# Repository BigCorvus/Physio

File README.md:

# Physio

My take on an (almost) open source development platform for a versatile wireless monitoring device that combines ECG, impedance pneumography, photoplethysmography, SPO2 calculation, galvanic skin response, NIBP wrist measurement as well as well as body temperature measurement in one wearable. 

Physio is based on a CK101 wrist blood pressure monitor, a CMS50C pulse oximeter, an ADS1292R analog front end for ECG and impedance pneumography (respiration monitoring via ECG electrodes), a MAX30205 human body temperature sensor and an ADXL345 accelerometer. The GSR measurement is also working fine so far, but it's interfering with the ADS1292R so only one of them can be used at a time. For instruction on hacking the CK101 and CMS50C see  my blog posts http://www.thinkering.de/cms/?p=833 and http://www.thinkering.de/cms/?p=864. and A Teensy 3.2 ties everythings together and uses an HC-05 bluetooth module for communication.
The carrier PCB of the current Physio version is designed for the great ADS1292R breakout board by protocentral->https://github.com/Protocentral/ADS1292rShield_Breakout

The Android app is based on the Amarino platform, so you have to download and install the Amarino App in order for this app to work (https://storage.googleapis.com/google-code-archive-downloads/v2/code.google.com/amarino/Amarino_2_v0_55.apk). The recording feature is not working yet and will be improved in the future.

In order to get the best ECG and respiration data I recommend placing the electrodes according to the "Einthoven II" lead.

Short demo video with crappy electrodes: https://youtu.be/U5jK3dh345U

Note: this is not a medical device, but a development platform for educational and research purposes. I'm assuming you know what you're doing.

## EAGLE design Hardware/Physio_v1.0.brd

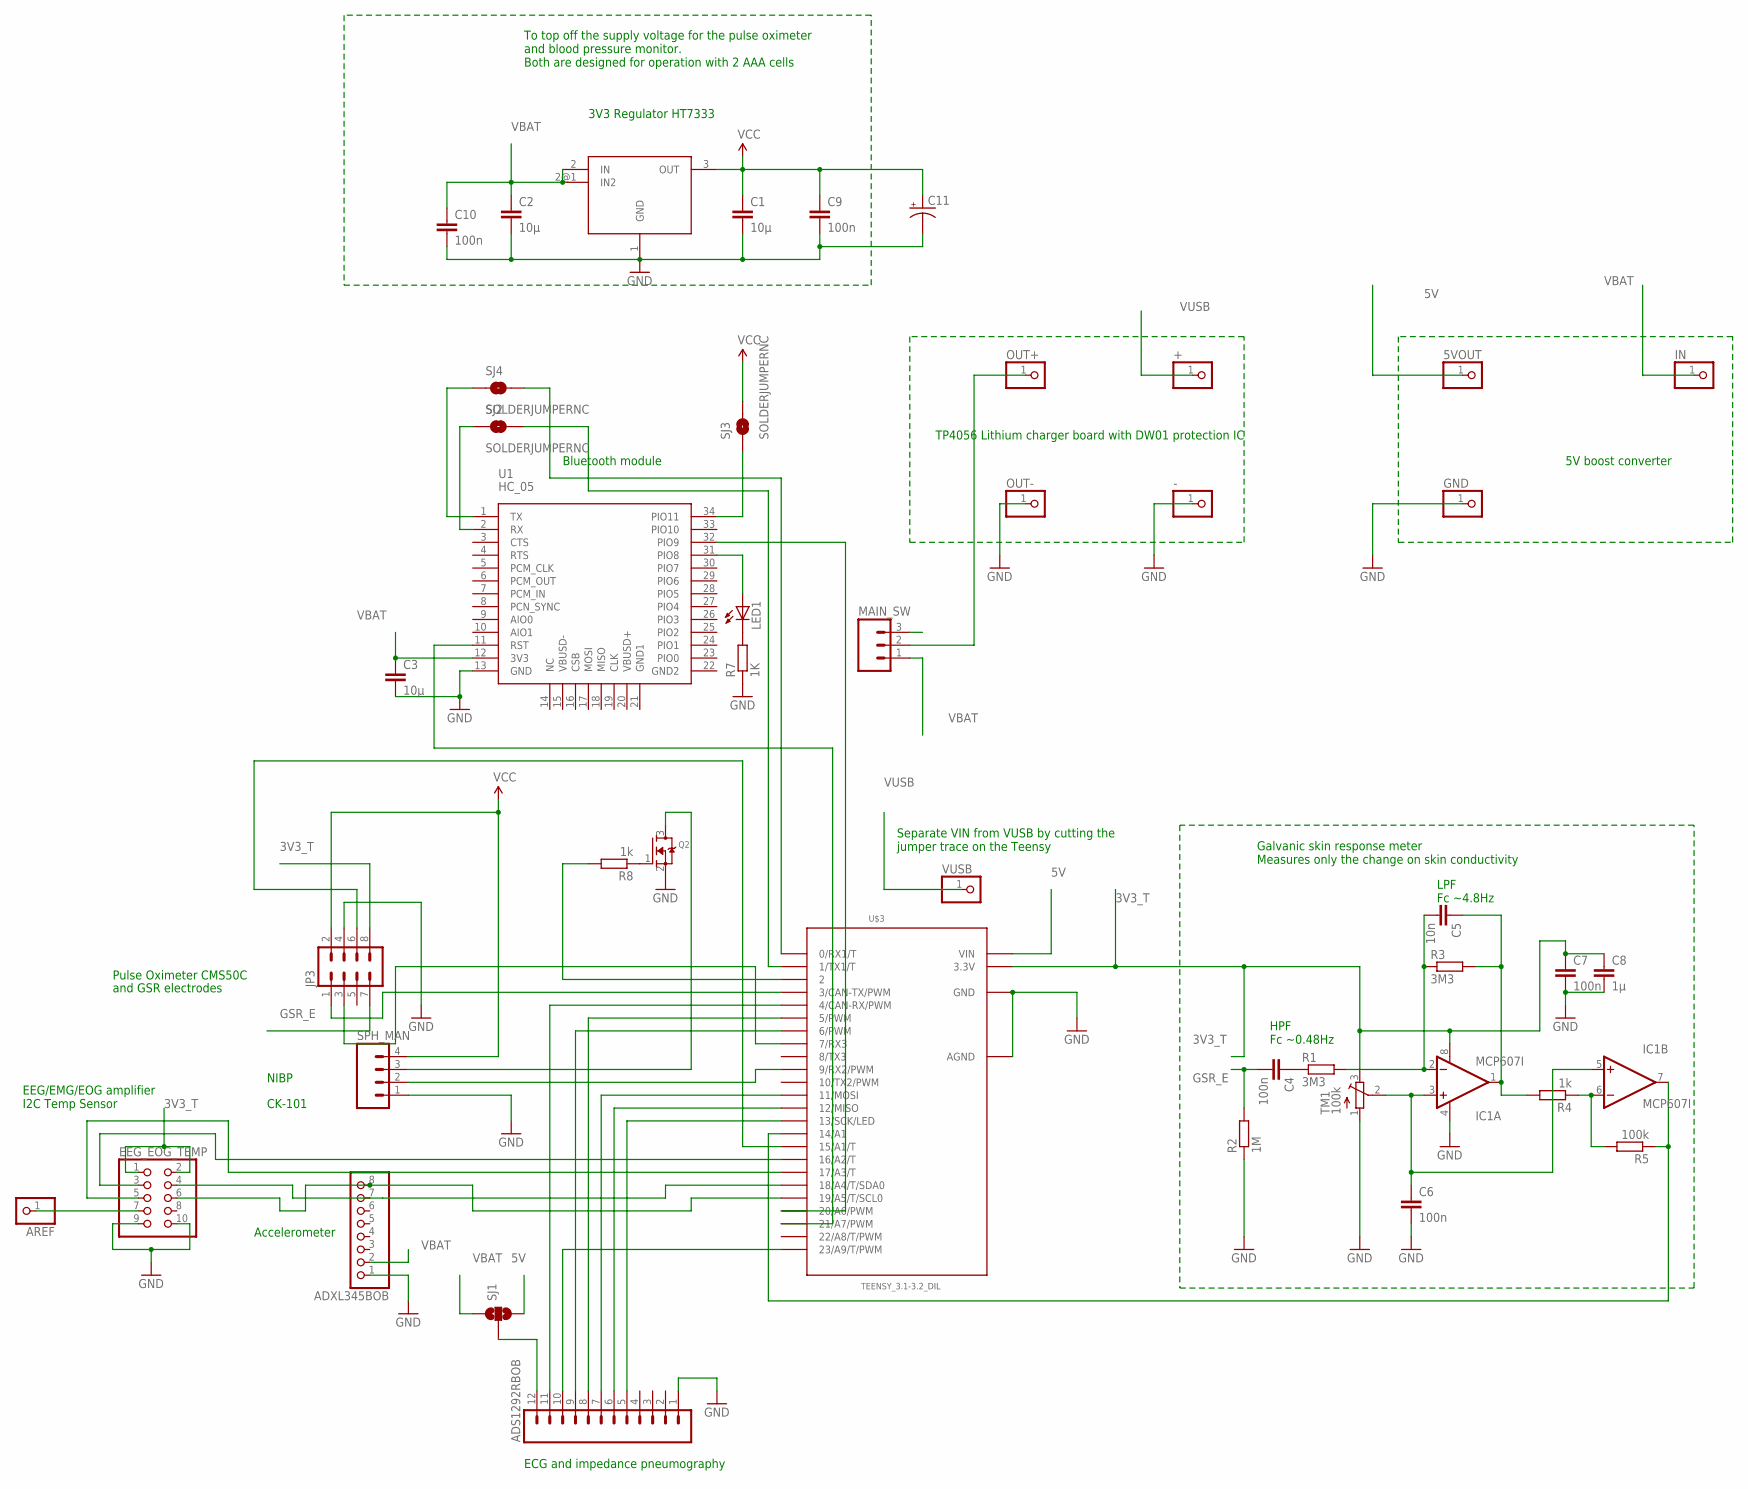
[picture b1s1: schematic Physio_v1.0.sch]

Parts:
5VOUT: PINHD-1X1; 1X01
+: PINHD-1X1; 1X01
-: PINHD-1X1; 1X01
ADS1292RBOB: M12PTH; 1X12
ADXL345BOB: PINHD-1X8CLEANBIG; 1X08-CLEANBIG
AREF: PINHD-1X1; 1X01
C1, C2, C3: 10µ; C0805K
C4, C6, C7, C9, C10: 100n; C0603K
C5: 10n; C0603K
C8: 1µ; C0603K
C11: CAP_POL7343; EIA7343
EEG_EOG_TEMP: PINHD-2X5/90; 2X05/90
GND: PINHD-1X1; 1X01
IC1: MCP607I; SO08
IN: PINHD-1X1; 1X01
JP3: M04X2; 2X4
LED1: LEDCHIP-LED0805; CHIP-LED0805
MAIN_SW: M03PTH; 1X03
OUT+: PINHD-1X1; 1X01
OUT-: PINHD-1X1; 1X01
Q2: MOSFET-NREFLOW; SOT23
R1, R3: 3M3; R0603
R2: 1M; R0603
R4, R8: 1k; R0603
R5: 100k; R0603
R7: 1K; R0603
SJ1: SOLDERJUMPER_2WAY-OLDT; SJ_2
SJ2, SJ3, SJ4: SOLDERJUMPERNC; SJ_2S
SPH_MAN: M04PTH; 1X04
TM1: 100k; TC33X
U1: HC_05; BLUETOOTH_SMD
U$2: HT7333; SOT89
U$3: TEENSY_3.1-3.2_DIL; TEENSY_3.0-3.2&LC_DIL
VUSB: PINHD-1X1; 1X01

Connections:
3V3_T: C7.1, C8.1, EEG_EOG_TEMP.1, EEG_EOG_TEMP.2, IC1.8 (V+), JP3.8, TM1.3 (E), U$3.3.3V
5V: 5VOUT.1, SJ1.3, U$3.VIN
GND: -.1, ADS1292RBOB.1, ADXL345BOB.1, C1.2, C2.2, C3.2, C6.2, C7.2, C8.2, C9.2, C10.2, C11.C (-), EEG_EOG_TEMP.9, EEG_EOG_TEMP.10, GND.1, IC1.4 (V-), JP3.4, OUT-.1, Q2.2 (S), R2.1, R7.1, SPH_MAN.1, TM1.1 (A), U1.13 (GND), U$2.1 (GND), U$3.AGND, U$3.GND
GSR_E: C4.2, JP3.7, R2.2
unnamed: JP3.1, U$3.3 (3/CAN-TX/PWM)
unnamed: SPH_MAN.2, U$3.9 (9/RX2/PWM)
unnamed: JP3.3, U$3.7 (7/RX3)
unnamed: Q2.3 (D), SPH_MAN.3
unnamed: SJ4.2, U$3.0 (0/RX1/T)
unnamed: SJ2.2, U$3.1 (1/TX1/T)
unnamed: ADS1292RBOB.7, U$3.11 (11/MOSI)
unnamed: ADS1292RBOB.6, U$3.12 (12/MISO)
unnamed: ADS1292RBOB.5, U$3.13 (13/SCK/LED)
unnamed: ADS1292RBOB.9, U$3.6 (6/PWM)
unnamed: ADS1292RBOB.8, U$3.5 (5/PWM)
unnamed: ADS1292RBOB.11, U$3.4 (4/CAN-RX/PWM)
unnamed: ADS1292RBOB.10, U$3.23/A9 (23/A9/T/PWM)
unnamed: C5.2, IC1.2 (-IN), R1.2, R3.1
unnamed: C5.1, IC1.1 (OUT), R3.2, R4.2
unnamed: C6.1, IC1.3 (+IN), IC1.5 (+IN), TM1.2 (S)
unnamed: C4.1, R1.1
unnamed: SJ4.1, U1.1 (TX)
unnamed: IC1.6 (-IN), R4.1, R5.2
unnamed: IC1.7 (OUT), R5.1, U$3.14/A0 (14/A1)
unnamed: SJ2.1, U1.2 (RX)
unnamed: JP3.6, U$3.15/A1 (15/A1/T)
unnamed: ADXL345BOB.8, EEG_EOG_TEMP.6, U$3.19/A5 (19/A5/T/SCL0)
unnamed: ADXL345BOB.7, EEG_EOG_TEMP.4, U$3.18/A4 (18/A4/T/SDA0)
unnamed: LED1.C, R7.2
unnamed: LED1.A, U1.31 (PIO8)
unnamed: EEG_EOG_TEMP.3, U$3.16/A2 (16/A2/T)
unnamed: EEG_EOG_TEMP.5, U$3.17/A3 (17/A3/T)
unnamed: R8.2, U$3.2
unnamed: ADS1292RBOB.12, SJ1.2
unnamed: Q2.1 (G), R8.1
unnamed: AREF.1, EEG_EOG_TEMP.7
unnamed: MAIN_SW.2, OUT+.1
unnamed: U1.32 (PIO9), U$3.20/A6 (20/A6/PWM)
unnamed: U1.11 (RST), U$3.21/A7 (21/A7/PWM)
unnamed: SJ3.1, U1.34 (PIO11)
VBAT: ADXL345BOB.2, C2.1, C3.1, C10.1, IN.1, MAIN_SW.1, SJ1.1, U1.12 (3V3), U$2.2 (IN), U$2.2@1 (IN2)
VCC: C1.1, C9.1, C11.A (+), JP3.2, SJ3.2, SPH_MAN.4, U$2.3 (OUT)
VUSB: +.1, VUSB.1

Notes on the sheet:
Galvanic skin response meter Measures only the change on skin conductivity
HPF Fc ~0.48Hz
LPF Fc ~4.8Hz
ECG and impedance pneumography
Accelerometer
NIBP
CK-101
Pulse Oximeter CMS50C
EEG/EMG/EOG amplifier I2C Temp Sensor
3V3 Regulator HT7333
Separate VIN from VUSB by cutting the jumper trace on the Teensy
TP4056 Lithium charger board with DW01 protection IC
5V boost converter
To top off the supply voltage for the pulse oximeter and blood pressure monitor. Both are designed for operation with 2 AAA cells
Bluetooth module
and GSR electrodes

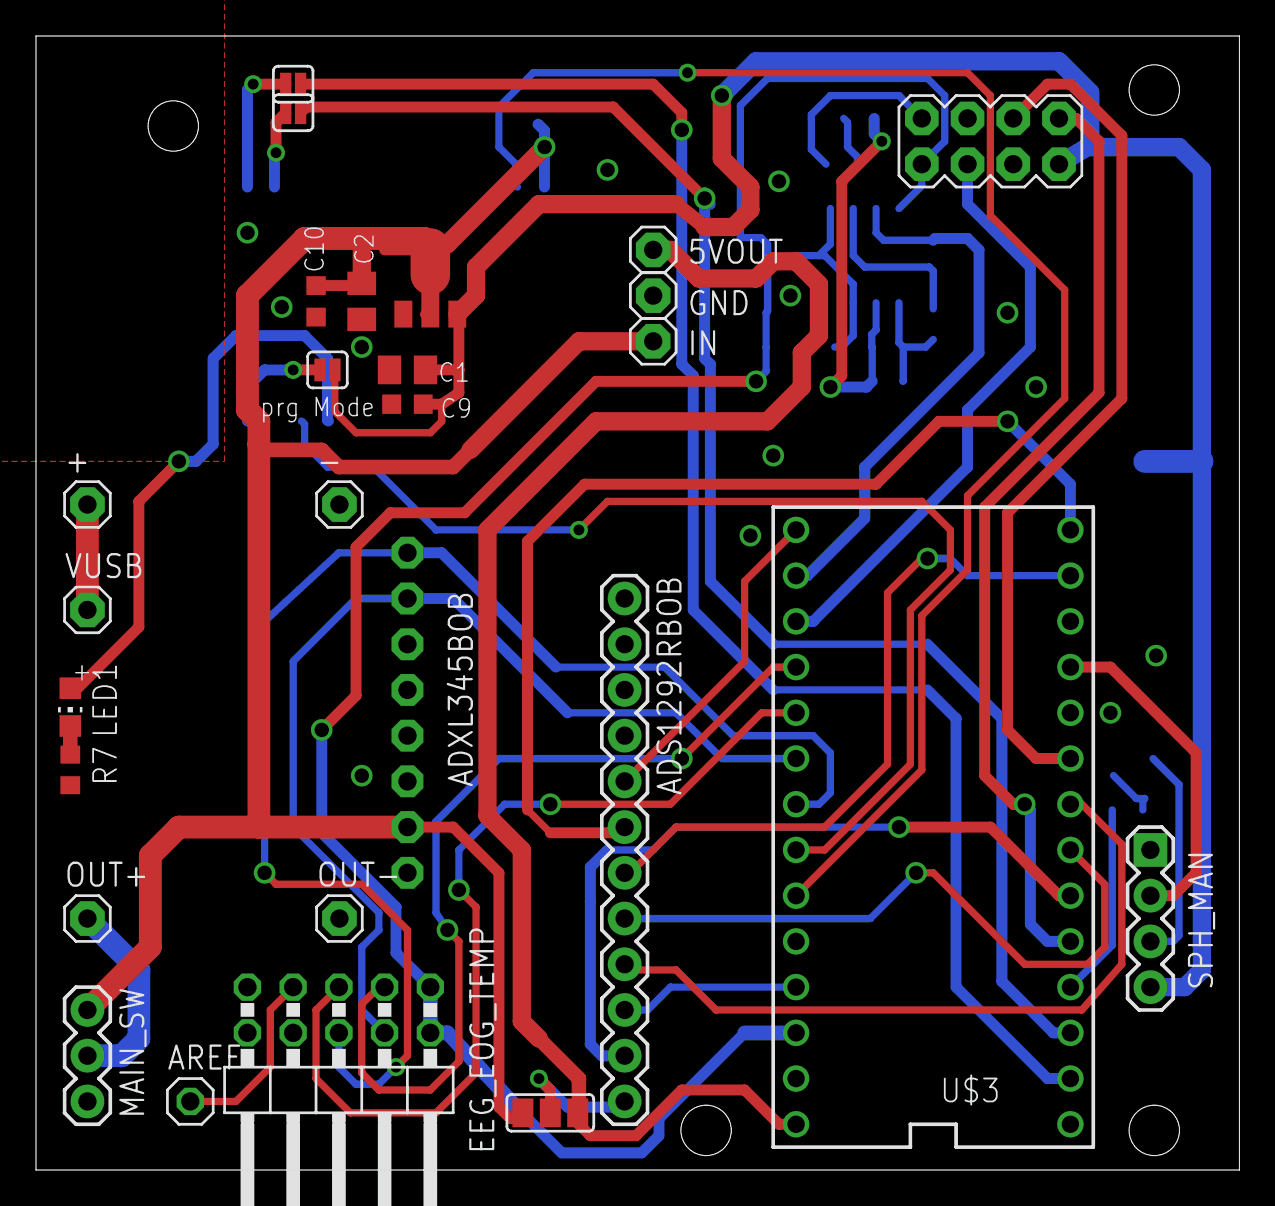
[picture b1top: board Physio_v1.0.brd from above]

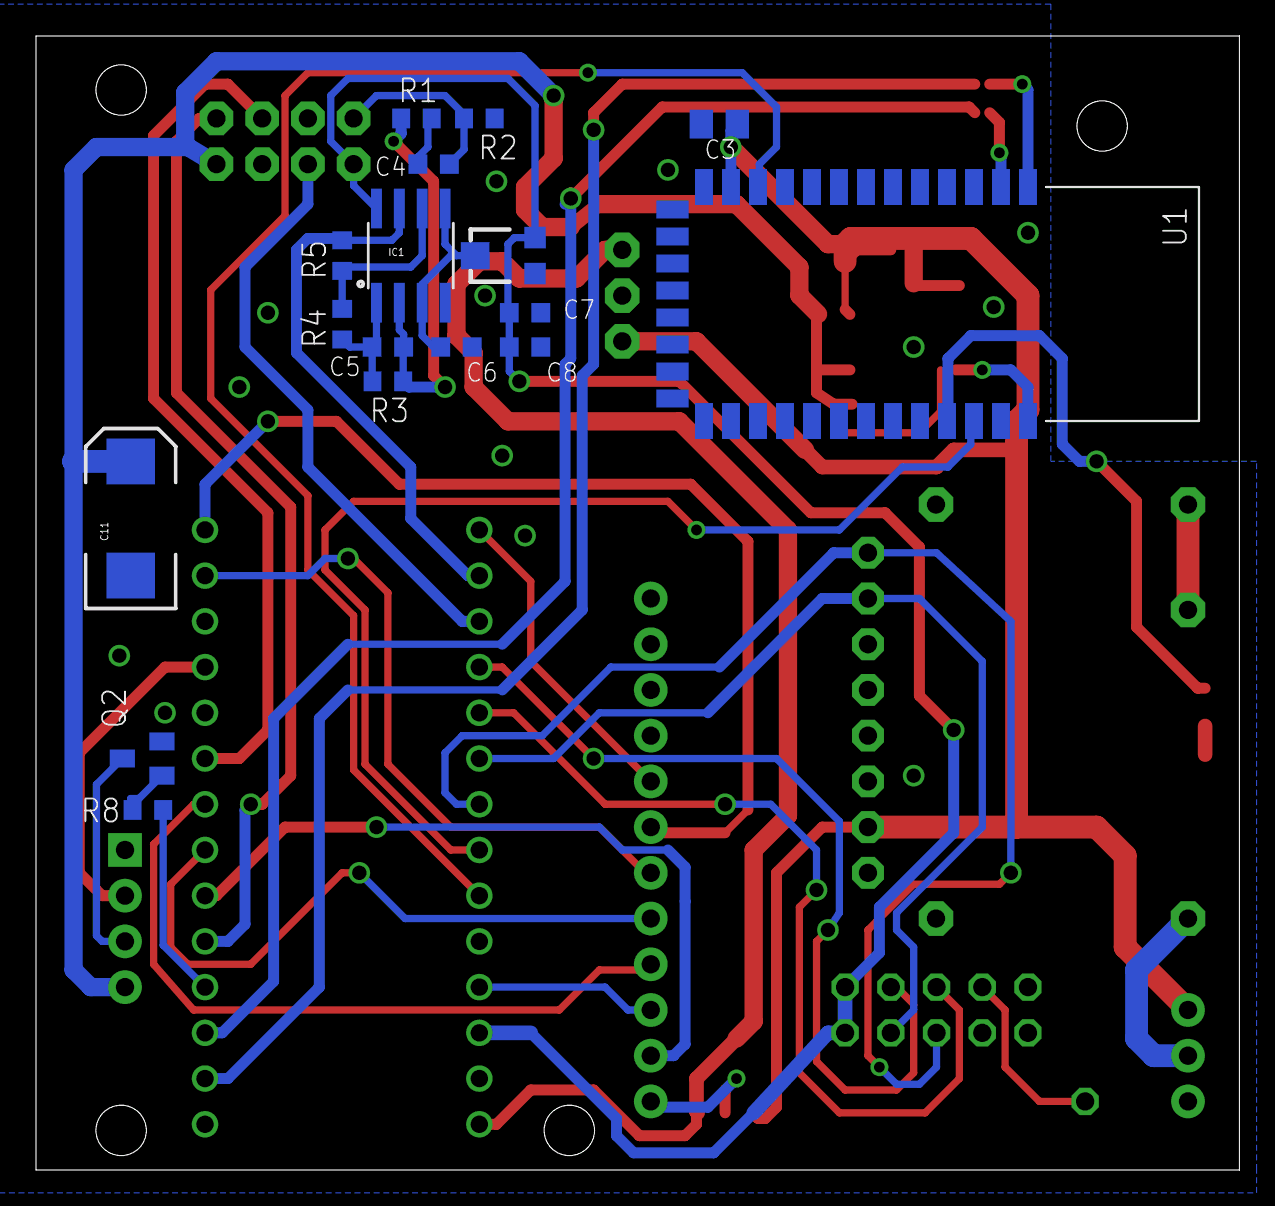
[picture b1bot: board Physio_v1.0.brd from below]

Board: 2 copper layers, 66.9 x 63.0 mm, 44 parts (17 on the bottom side), 43 nets.

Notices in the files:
parts and their libraries:
SparkFun-Connectors: Licensing: Creative Commons ShareAlike 4.0 International - https://creativecommons.org/licenses/by-sa/4.0
